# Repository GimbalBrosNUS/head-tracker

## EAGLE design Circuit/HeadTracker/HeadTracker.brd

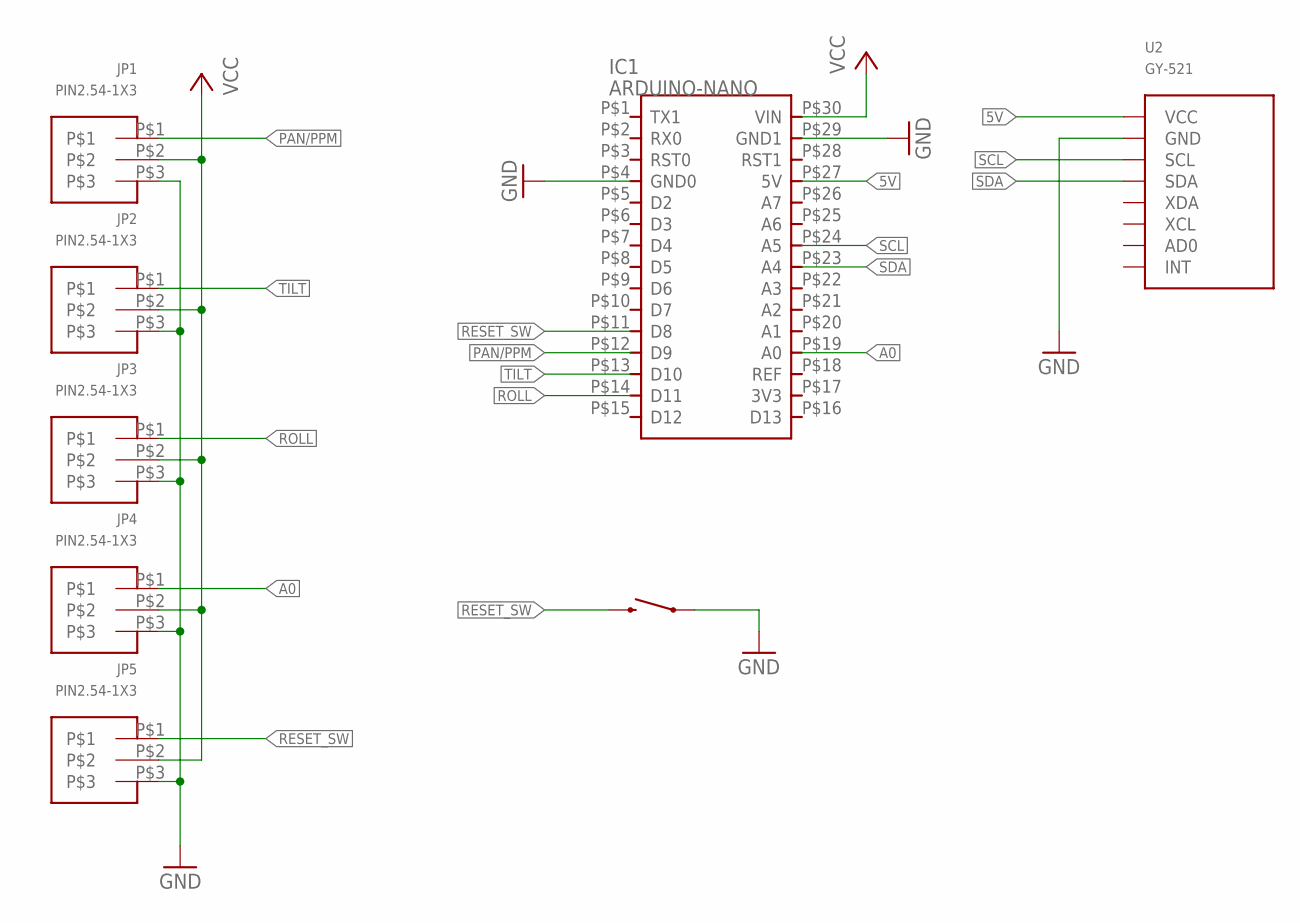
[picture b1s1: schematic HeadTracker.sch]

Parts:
IC1: ARDUINO-NANO
JP1, JP2, JP3, JP4, JP5: PIN2.54-1X3
S1: SWITCH-MOMENTARY-2PTH; TACTILE-PTH
U2: GY-521

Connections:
5V: IC1.P$27 (5V), U2.P$1 (VCC)
A0: IC1.P$19 (A0), JP4.P$1
GND: IC1.P$4 (GND0), IC1.P$29 (GND1), JP1.P$3, JP2.P$3, JP3.P$3, JP4.P$3, JP5.P$3, S1.1, U2.P$2 (GND)
PAN/PPM: IC1.P$12 (D9), JP1.P$1
RESET_SW: IC1.P$11 (D8), JP5.P$1, S1.3 (2)
ROLL: IC1.P$14 (D11), JP3.P$1
SCL: IC1.P$24 (A5), U2.P$3 (SCL)
SDA: IC1.P$23 (A4), U2.P$4 (SDA)
TILT: IC1.P$13 (D10), JP2.P$1
VCC: IC1.P$30 (VIN), JP1.P$2, JP2.P$2, JP3.P$2, JP4.P$2, JP5.P$2

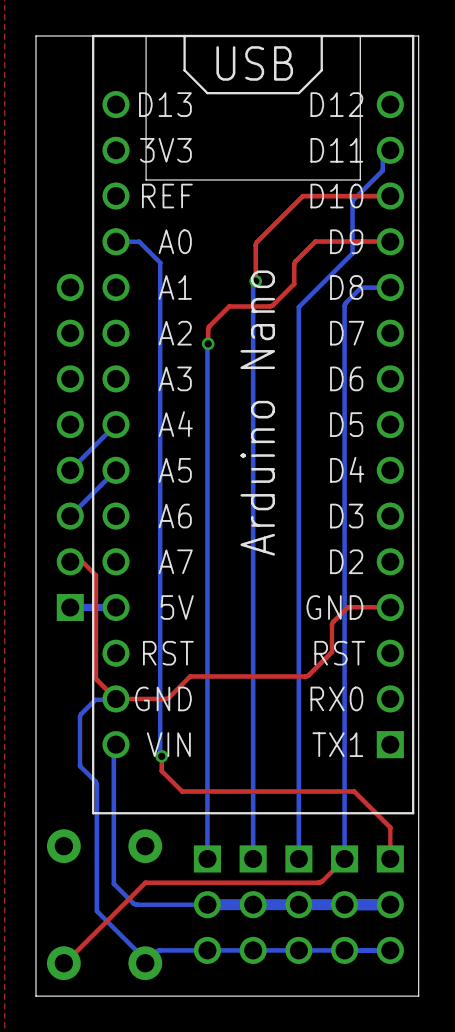
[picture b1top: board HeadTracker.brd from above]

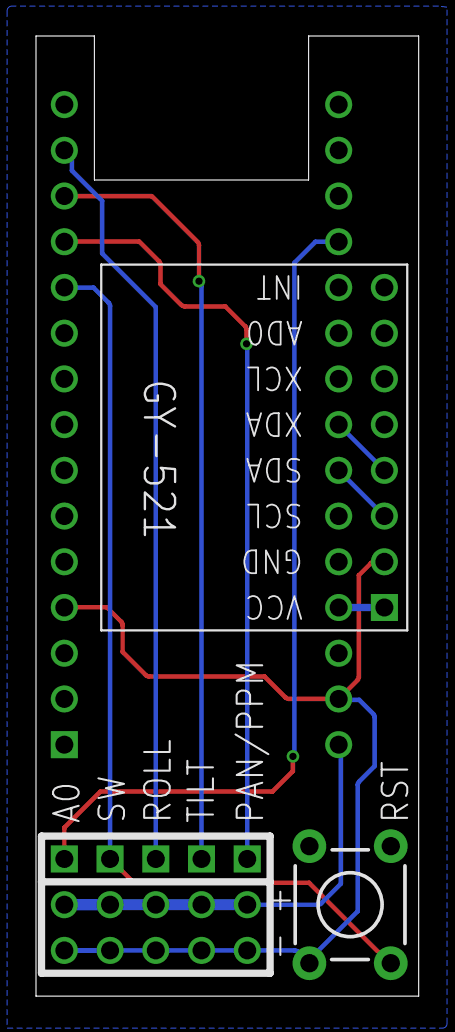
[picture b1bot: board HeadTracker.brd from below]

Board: 2 copper layers, 21.3 x 53.3 mm, 8 parts (7 on the bottom side), 10 nets.

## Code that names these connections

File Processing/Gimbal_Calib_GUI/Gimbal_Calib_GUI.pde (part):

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        if(!ssPan.reverse ) BtnPanReverse.setOff();  else BtnPanReverse.setOn();
        if(!ssTilt.reverse) BtnTiltReverse.setOff(); else BtnTiltReverse.setOn();
        if(!ssRoll.reverse) BtnRollReverse.setOff(); else BtnRollReverse.setOn();        
        if(bOutputTypePPM == true) BtnPPM.setCaptionLabel("PPM"); else BtnPPM.setCaptionLabel("PWM");
      }  
      else if(serial_values[0].equals("WP")){
        if(iExecCMDID == 21)iExecCMDID = 0;
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        if(!bOutputTypePPM){
          bOutputTypePPM = true;
          //theEvent.getController().setCaptionLabel("disconnect");
          BtnPPM.setCaptionLabel("PPM");
        }else{
          bOutputTypePPM = false;
          BtnPPM.setCaptionLabel("PWM");
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        ssRoll.ppm_max = 2000;
        ssRoll.reverse = false;
        bOutputTypePPM = true;
        BtnPPM.setCaptionLabel("PPM");
        InitializeParameterValues();
        break;
        
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                      .setOpen(false)
                      .setId(52);
  DlTiltCh         = cp.addScrollableList("Tilt Ch")
                      .setLabel("Tilt")
                      .setPosition(650,255)
                      .setBackgroundColor(color(190))
                      .setItemHeight(20)
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                      .setOpen(false)
                      .setId(53);
  DlRollCh         = cp.addScrollableList("Roll Ch")
                      .setLabel("Roll")
                      .setPosition(700,255)
                      .setBackgroundColor(color(190))
                      .setItemHeight(20)
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
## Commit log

2017-09-15 update exe files

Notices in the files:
Processing/Gimbal_Calib_GUI/Gimbal_Calib_GUI.pde:
Copyright (c) 2017 Smart System Institute, National University of Singapore, LLC
parts and their libraries:
SparkFun-Electromechanical: Licensing: Creative Commons ShareAlike 4.0 International - https://creativecommons.org/licenses/by-sa/4.0
